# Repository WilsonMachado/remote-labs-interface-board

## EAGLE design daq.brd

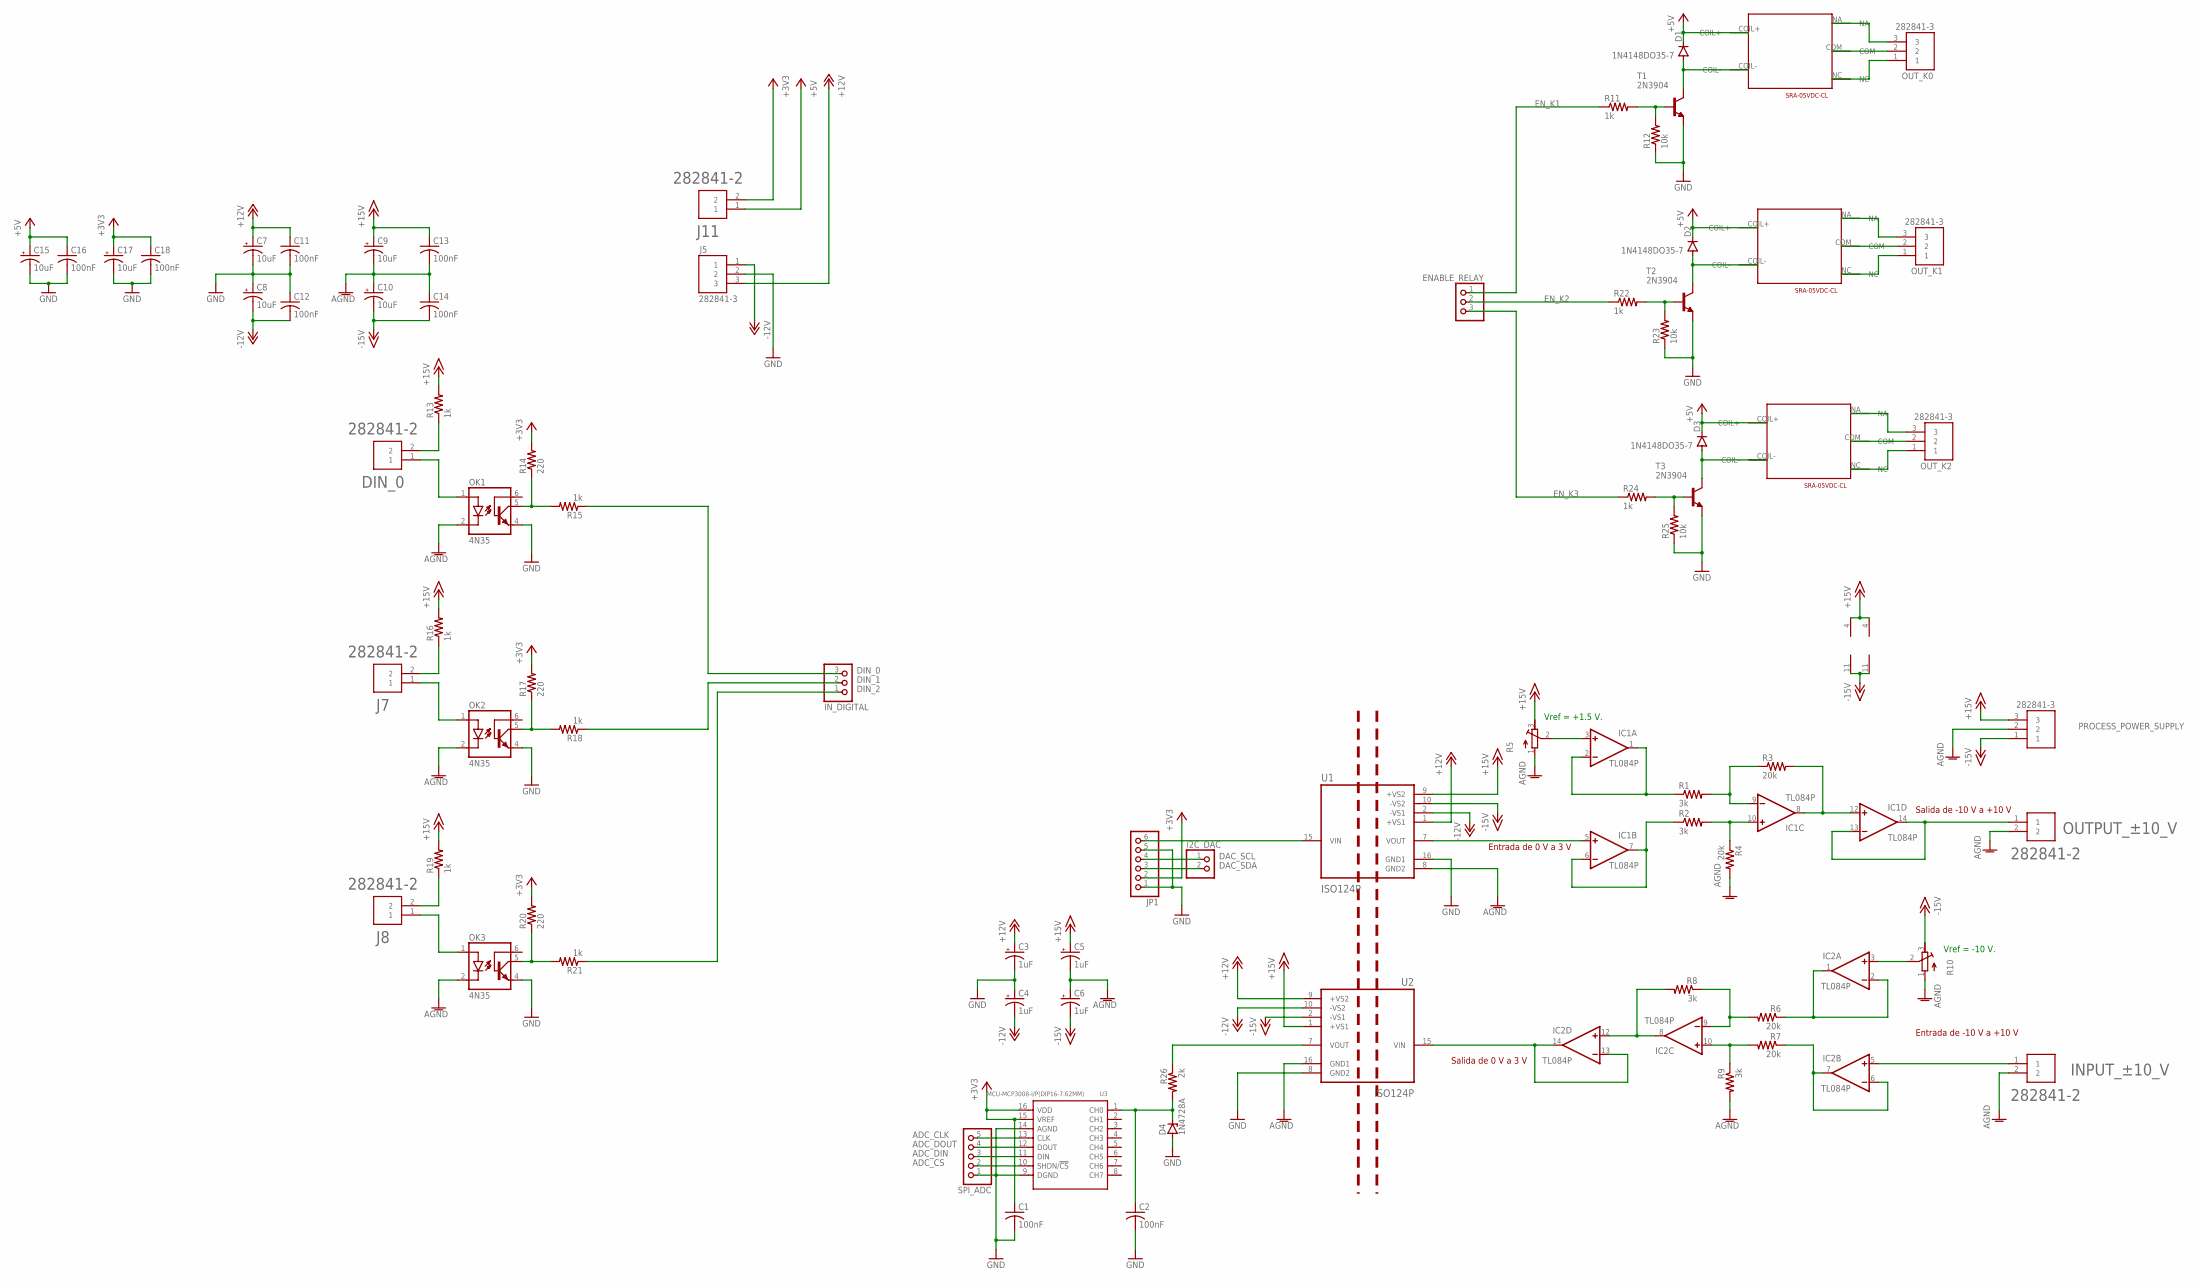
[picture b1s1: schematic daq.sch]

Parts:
C1, C2, C11, C12, C13, C14, C16, C18: 100nF; C025-025X050
C3, C4, C5, C6: 1uF; E2-5
C7, C8, C9, C10, C15, C17: 10uF; E2-5
D1, D2, D3: 1N4148DO35-7; DO35-7
D4: 1N4728A; DO41Z10
DIN_0: 282841-2; TE_282841-2
ENABLE_RELAY: PINHD-1X3; 1X03
I2C_DAC: PINHD-1X2; 1X02
IC1, IC2: TL084P; DIL14
INPUT_±10_V: 282841-2; TE_282841-2
IN_DIGITAL: PINHD-1X3; 1X03
J5: 282841-3; TE_282841-3
J7, J8, J11: 282841-2; TE_282841-2
JP1: PINHD-1X6; 1X06
OK1, OK2, OK3: 4N35; DIL06
OUTPUT_±10_V: 282841-2; TE_282841-2
OUT_K0, OUT_K1, OUT_K2: 282841-3; TE_282841-3
PROCESS_POWER_SUPPLY: 282841-3; TE_282841-3
R1, R2, R8, R9: 3k; 0207/10
R3, R4, R6, R7: 20k; 0207/10
R5, R10: R-TRIMM64W; RTRIM64W
R11, R13, R15, R16, R18, R19, R21, R22, R24: 1k; 0207/10
R12, R23, R25: 10k; 0207/10
R14, R17, R20: 220; 0207/10
R26: 2k; 0207/10
SPI_ADC: PINHD-1X5; 1X05
T1, T2, T3: 2N3904; TO92
U1, U2: ISO124P; DIP763W46P254L2134H533Q8_16
U3: MCU-MCP3008-I/P(DIP16-7.62MM); DIP16-2.54-19.2X7.62MM
U$1, U$2, U$3: SRA-05VDC-CL

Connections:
+3V3: C1.1, C17.+, C18.1, J11.2, JP1.2, R14.2, R17.2, R20.2, U3.15 (VREF), U3.16 (VDD)
+5V: C15.+, C16.1, D1.C, D2.C, D3.C, J11.1, U$1.COIL+, U$2.COIL+, U$3.COIL+
+12V: C3.+, C7.+, C11.1, J5.3, U1.1 (+VS1), U2.9 (+VS2)
+15V: C5.+, C9.+, C13.1, IC1.4 (V+), IC2.4 (V+), PROCESS_POWER_SUPPLY.3, R5.3 (E), R13.2, R16.2, R19.2, U1.9 (+VS2), U2.1 (+VS1)
-12V: C4.-, C8.-, C12.2, J5.1, U1.2 (-VS1), U2.10 (-VS2)
-15V: C6.-, C10.-, C14.2, IC1.11 (V-), IC2.11 (V-), PROCESS_POWER_SUPPLY.1, R10.3 (E), U1.10 (-VS2), U2.2 (-VS1)
ADC_CLK: SPI_ADC.5, U3.13 (CLK)
ADC_CS: SPI_ADC.2, U3.10 (SHDN/!CS)
ADC_DIN: SPI_ADC.3, U3.11 (DIN)
ADC_DOUT: SPI_ADC.4, U3.12 (DOUT)
AGND: C5.-, C6.+, C9.-, C10.+, C13.2, C14.1, INPUT_±10_V.2, OK1.2 (C), OK2.2 (C), OK3.2 (C), OUTPUT_±10_V.2, PROCESS_POWER_SUPPLY.2, R4.2, R5.1 (A), R9.2, R10.1 (A), U1.8 (GND2), U2.16 (GND1)
DAC_SCL: I2C_DAC.1, JP1.4
DAC_SDA: I2C_DAC.2, JP1.3
DIN_0: IN_DIGITAL.3, R15.1
DIN_1: IN_DIGITAL.2, R18.1
DIN_2: IN_DIGITAL.1, R21.1
EN_K1: ENABLE_RELAY.1, R11.1
EN_K2: ENABLE_RELAY.2, R22.1
EN_K3: ENABLE_RELAY.3, R24.1
GND: C1.2, C2.2, C3.-, C4.+, C7.-, C8.+, C11.2, C12.1, C15.-, C16.2, C17.-, C18.2, D4.A, J5.2, JP1.1, JP1.5, OK1.4 (EMI), OK2.4 (EMI), OK3.4 (EMI), R12.1, R23.1, R25.1, SPI_ADC.1, T1.3 (E), T2.3 (E), T3.3 (E), U1.16 (GND1), U2.8 (GND2), U3.9 (DGND), U3.14 (AGND)
unnamed: IC1.9 (-IN), R1.2, R3.1
unnamed: IC1.10 (+IN), R2.2, R4.1
unnamed: IC1.1 (OUT), IC1.2 (-IN), R1.1
unnamed: IC1.8 (OUT), IC1.12 (+IN), R3.2
unnamed: IC1.6 (-IN), IC1.7 (OUT), R2.1
unnamed: IC1.13 (-IN), IC1.14 (OUT), OUTPUT_±10_V.1
unnamed: IC1.3 (+IN), R5.2 (S)
unnamed: IC2.9 (-IN), R6.2, R8.1
unnamed: IC2.10 (+IN), R7.2, R9.1
unnamed: IC2.8 (OUT), IC2.12 (+IN), R8.2
unnamed: IC2.1 (OUT), IC2.2 (-IN), R6.1
unnamed: IC2.6 (-IN), IC2.7 (OUT), R7.1
unnamed: IC2.13 (-IN), IC2.14 (OUT), U2.15 (VIN)
unnamed: IC2.3 (+IN), R10.2 (S)
unnamed: IC1.5 (+IN), U1.7 (VOUT)
unnamed: IC2.5 (+IN), INPUT_±10_V.1
unnamed: C2.1, D4.C, R26.2, U3.1 (CH0)
unnamed: JP1.6, U1.15 (VIN)
unnamed: D1.A, T1.1 (C), U$1.COIL-
unnamed: R11.2, R12.2, T1.2 (B)
unnamed: OUT_K0.3, U$1.NA
unnamed: OUT_K0.2, U$1.COM
unnamed: OUT_K0.1, U$1.NC
unnamed: DIN_0.1, OK1.1 (A)
unnamed: DIN_0.2, R13.1
unnamed: OK1.5 (COL), R14.1, R15.2
unnamed: J7.1, OK2.1 (A)
unnamed: J7.2, R16.1
unnamed: OK2.5 (COL), R17.1, R18.2
unnamed: J8.1, OK3.1 (A)
unnamed: J8.2, R19.1
unnamed: OK3.5 (COL), R20.1, R21.2
unnamed: D2.A, T2.1 (C), U$2.COIL-
unnamed: OUT_K1.3, U$2.NA
unnamed: OUT_K1.2, U$2.COM
unnamed: OUT_K1.1, U$2.NC
unnamed: R22.2, R23.2, T2.2 (B)
unnamed: D3.A, T3.1 (C), U$3.COIL-
unnamed: OUT_K2.3, U$3.NA
unnamed: OUT_K2.2, U$3.COM
unnamed: OUT_K2.1, U$3.NC
unnamed: R24.2, R25.2, T3.2 (B)
unnamed: R26.1, U2.7 (VOUT)

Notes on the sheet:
Vref = -10 V.
Vref = +1.5 V.
Entrada de -10 V a +10 V
Salida de -10 V a +10 V
Salida de 0 V a 3 V
Entrada de 0 V a 3 V

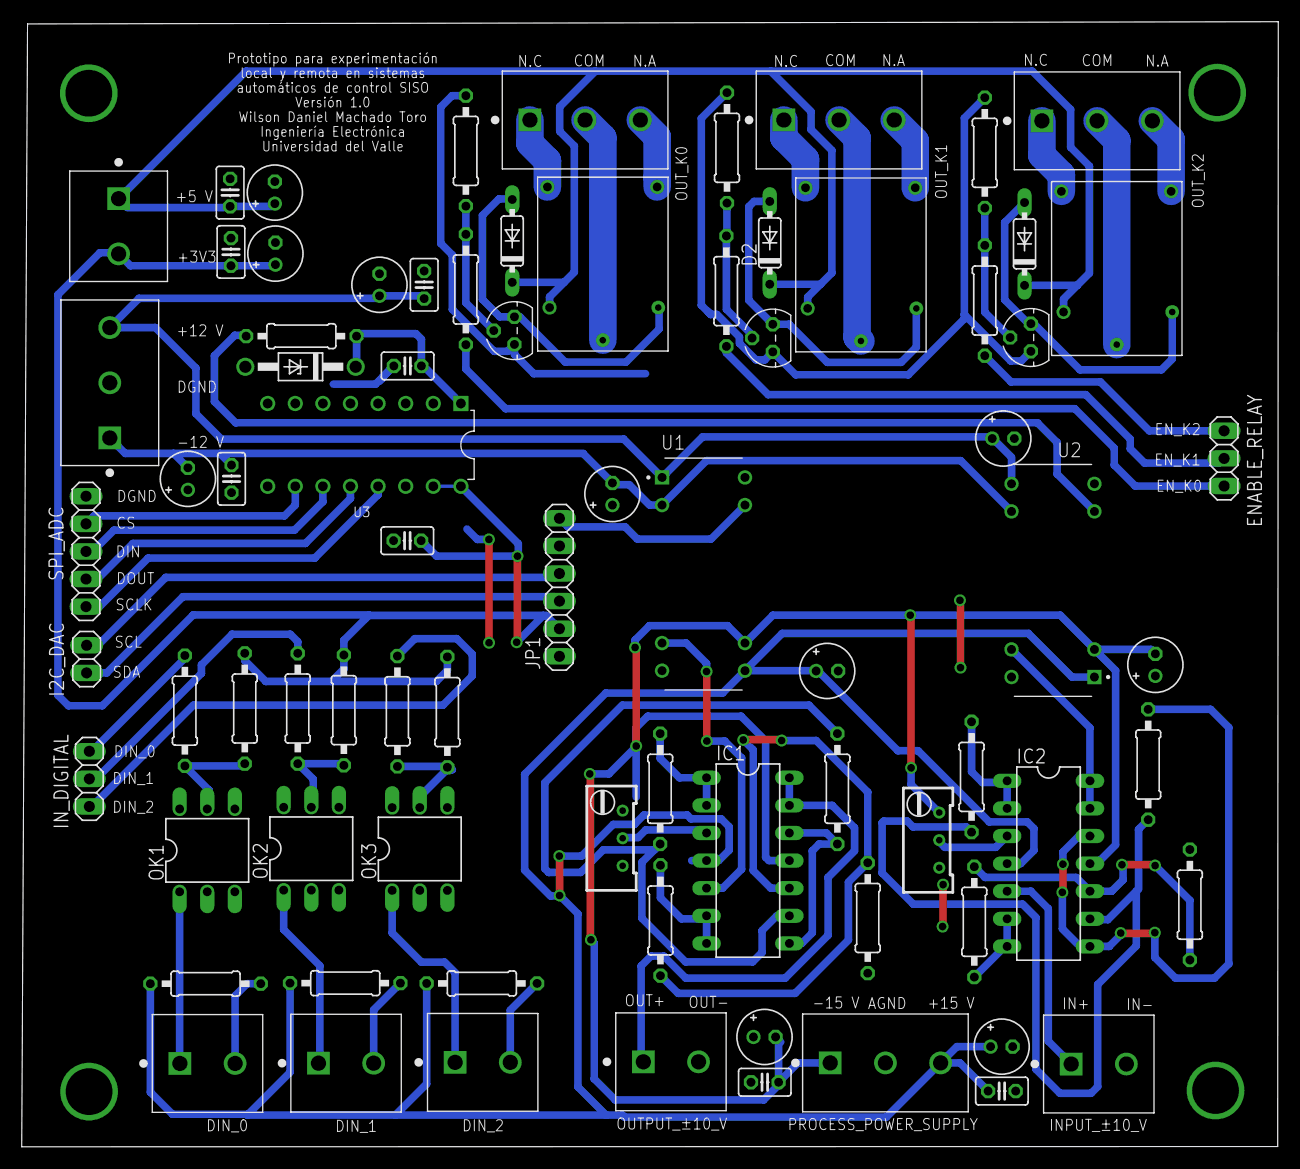
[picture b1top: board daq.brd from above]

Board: 2 copper layers, 115.6 x 103.5 mm, 78 parts (0 on the bottom side), 63 nets.

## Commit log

2022-06-21 Version actual de la tarjeta de interfaz para el control del servomecanismo. Hace parte de mi TG. Tiene todas las modificaciones con las que trabaja la primera versión que hice casera.
